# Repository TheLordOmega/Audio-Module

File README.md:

Audio Module 
A module that can play sound over 3.5mm , speaker with adjustable volume with a knob
Key features:
- a knob
- a 2w speaker
- 3.5mm jack
- no storage

## PCB

## Schematic

## 3D Case

## Bill of Materials (excluding console)

Also found in [bom.csv](./bom.csv).

| Item                                                  | Price per unit | Nr of units | Total price | Link                                               |
| ----------------------------------------------------- | -------------- | ----------- | ----------- | -------------------------------------------------- |
| PCB                                                   |                | 1           | 10$         | -                                                  |
| 2x7 2.54mm pin header (J1 breakout board)             | ~$0.20-0.39    | 1           | ~$0.20-0.39 | https://www.aliexpress.com/item/4000186187780.html |
| 3-pin flying-lead connector (JST-PH or Dupont header) |                | 1           | -           | -                                                  |
| MD0/MD1 ID resistors, 0603                            |                | 2           | -           | -                                                  |
| a volume knob                                         |                | 1           | -           | -                                                  |
|                                                       |                |             |             |                                                    |
| **Total**                                             |                |             | 10$         |                                                    |

## Credits

* Driver: [`xpanse_api`](https://docs.rs/xpanse-api)
* Thanks to Hack Club and the Hackxpansion team for the console platform this module plugs into: https://github.com/hackclub/hackxpansion

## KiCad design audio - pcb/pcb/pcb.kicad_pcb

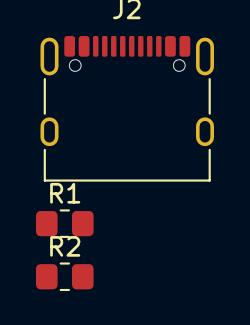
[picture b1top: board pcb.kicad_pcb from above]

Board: 2 copper layers, 3 parts (0 on the bottom side), 3 nets, no tracks yet.

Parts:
J2: USB_C_Receptacle_USB2.0_16P; USB_C_Receptacle_XKB_U262-16XN-4BVC11
R1, R2: R; R_0805_2012Metric_Pad1.20x1.40mm_HandSolder

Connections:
+3.3V: R1.1, R2.1
unnamed: J2.A1 (GND), J2.A12 (GND), J2.B1 (GND), J2.B12 (GND)
unnamed: J2.A4 (VBUS), J2.A9 (VBUS), J2.B4 (VBUS), J2.B9 (VBUS)

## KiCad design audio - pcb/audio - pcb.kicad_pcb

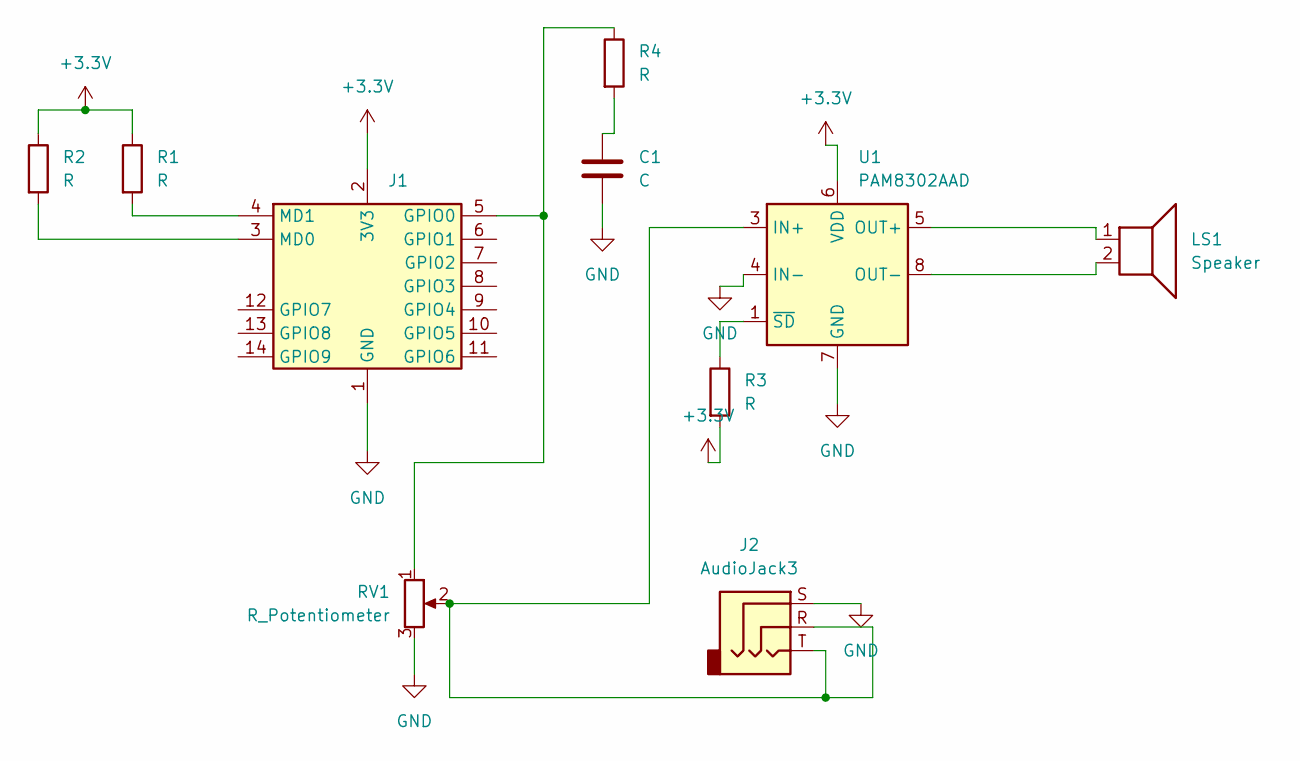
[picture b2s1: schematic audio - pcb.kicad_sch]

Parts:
C1: C; C_Disc_D5.0mm_W2.5mm_P5.00mm
J1: Male_Module
J2: AudioJack3; Jack_3.5mm_CUI_SJ-3523-SMT_Horizontal
LS1: Speaker; JST_EH_B2B-EH-A_1x02_P2.50mm_Vertical
R1, R2, R3, R4: R; R_0603_1608Metric
RV1: R_Potentiometer; Potentiometer_Piher_PC-16_Single_Vertical
U1: PAM8302AAD; SOIC-8_3.9x4.9mm_P1.27mm

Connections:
+3.3V: J1.2 (3V3), R1.1, R2.1, R3.2, U1.6 (VDD)
GND: C1.2, J1.1 (GND), J2.S, RV1.3, U1.4 (IN-), U1.7 (GND)
unnamed: C1.1, R4.2
unnamed: J1.5 (GPIO0), R4.1, RV1.1
unnamed: J1.3 (MD0), R2.2
unnamed: J1.4 (MD1), R1.2
unnamed: J2.R, J2.T, RV1.2, U1.3 (IN+)
unnamed: LS1.1, U1.5 (OUT+)
unnamed: LS1.2, U1.8 (OUT-)
unnamed: R3.1, U1.1 (~SD)

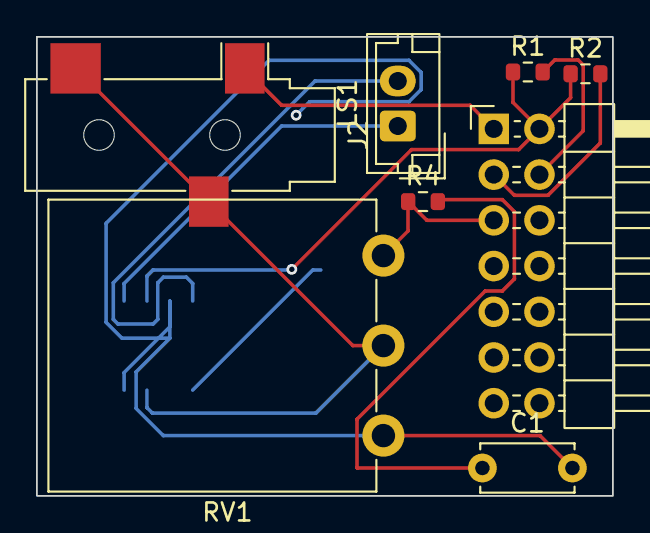
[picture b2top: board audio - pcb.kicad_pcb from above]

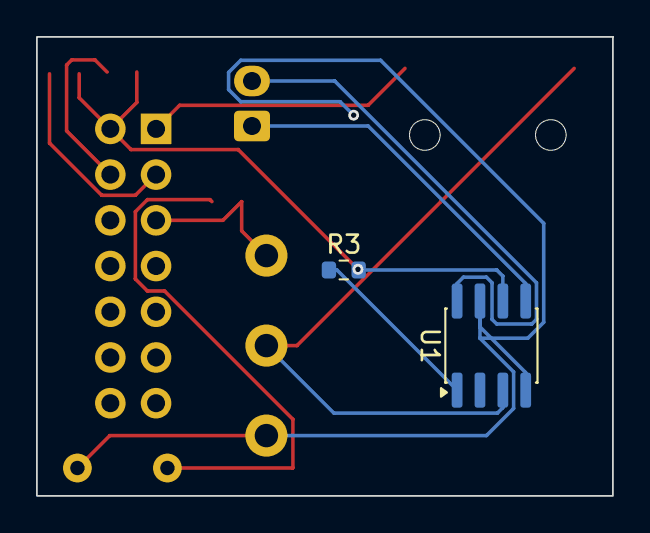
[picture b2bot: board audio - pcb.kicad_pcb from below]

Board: 2 copper layers, 32.0 x 25.5 mm, 10 parts (2 on the bottom side), 10 nets.
